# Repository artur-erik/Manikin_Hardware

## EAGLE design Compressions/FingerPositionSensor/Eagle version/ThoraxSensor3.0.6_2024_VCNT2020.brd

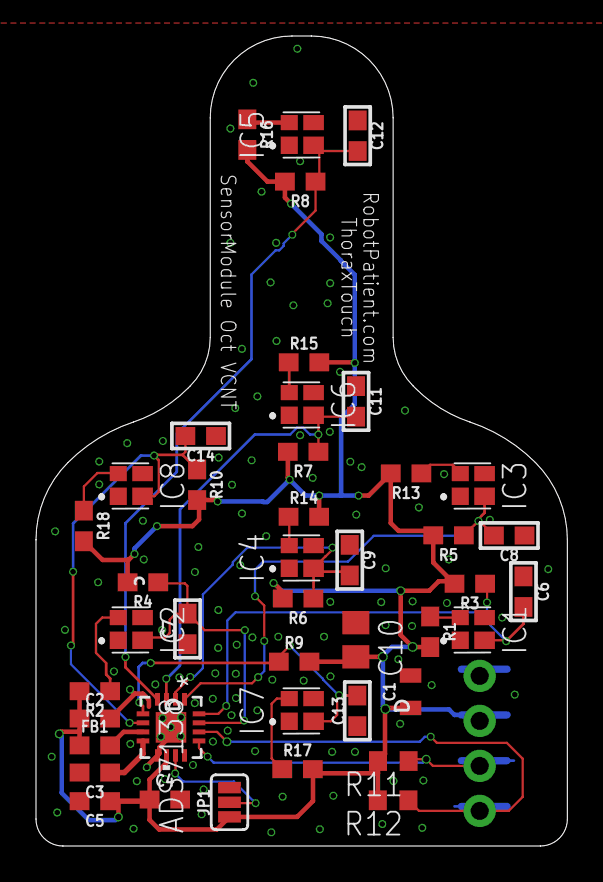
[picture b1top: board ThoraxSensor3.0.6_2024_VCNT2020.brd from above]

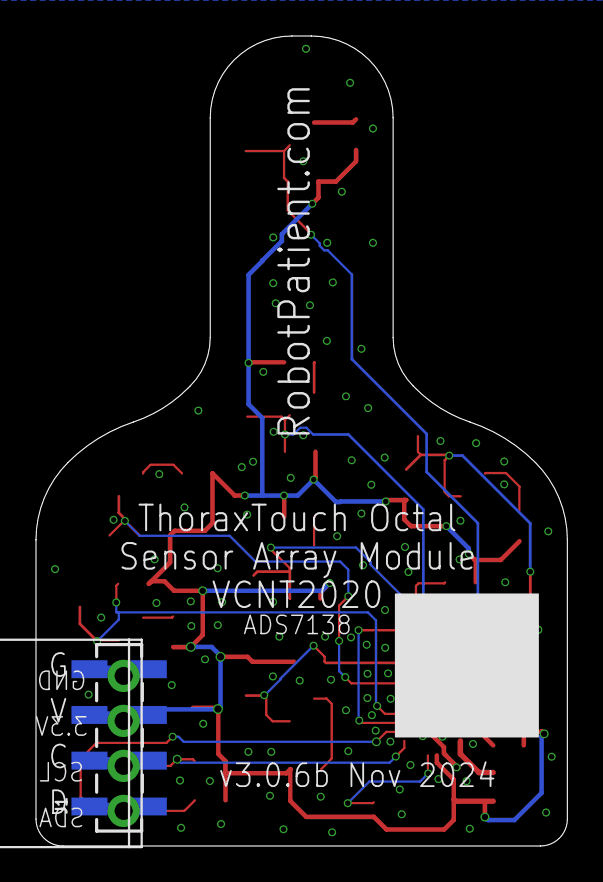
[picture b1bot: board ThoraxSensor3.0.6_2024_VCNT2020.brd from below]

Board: 2 copper layers, 29.5 x 45.0 mm, 45 parts (2 on the bottom side), 23 nets.

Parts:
C1: 10uF; 0805
C2, C3, C4: 1.0uF; 0603
C5: 100pF; 0603
C6, C7, C8, C9, C11, C12, C13, C14: 0.1uF; 0603
C10: 10µF; C0805
FB1: 30Ω; 0603
IC1, IC2, IC3, IC4, IC5, IC6, IC7, IC8: VCNT2020
J1: 1X04_SMD_STRAIGHT_COMBO; 1X04_SMD_VERTICAL_COMBO
JP1: JUMPER-SMT_3_1-NC_PASTE_SILK; SMT-JUMPER_3_1-NC_PASTE_SILK
R1, R2, R13, R14, R15, R16, R17, R18: 180; 0603
R3, R4, R5, R6, R7, R8, R9, R10: 10k; 0603
R11, R12: 4k7; R0603
U$9: ADS7138; QFN_8IRTER_TEX
U$13: PHOENIX_PTSM_M4_TH_ANGLEMIRRORED_SILK_I2C; PTSM_M4_TH_ANGLE_NEUTRAL_MIRRORED

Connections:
3.3V: C1.1, C2.1, C4.1, C5.1, C10.2, FB1.1, J1.3, JP1.1, R1.2, R2.2, R3.2, R4.2, R5.2, R6.2, R7.2, R8.2, R9.2, R10.2, R11.2, R12.2, R13.2, R14.2, R15.2, R16.2, R17.2, R18.2, U$9.10, U$13.P2
ADDR: JP1.2, U$9.11
DECAP: C3.1, U$9.8
GND: C1.2, C2.2, C3.2, C4.2, C5.2, C6.1, C7.1, C8.1, C9.1, C10.1, C11.1, C12.1, C13.1, C14.1, IC1.1, IC1.4, IC2.1, IC2.4, IC3.1, IC3.4, IC4.1, IC4.4, IC5.1, IC5.4, IC6.1, IC6.4, IC7.1, IC7.4, IC8.1, IC8.4, J1.4, JP1.3, U$9.9, U$9.17, U$13.P1
unnamed: IC1.3, R1.1
unnamed: IC2.3, R2.1
unnamed: IC3.3, R13.1
unnamed: IC4.3, R14.1
unnamed: IC6.3, R15.1
unnamed: IC5.3, R16.1
unnamed: IC7.3, R17.1
unnamed: IC8.3, R18.1
unnamed: FB1.2, U$9.7
S1: C6.2, IC1.2, R3.1, U$9.16
S2: C7.2, IC2.2, R4.1, U$9.15
S3: C8.2, IC3.2, R5.1, U$9.1
S4: C9.2, IC4.2, R6.1, U$9.2
S5: C11.2, IC6.2, R7.1, U$9.3
S6: C12.2, IC5.2, R8.1, U$9.4
S7: C13.2, IC7.2, R9.1, U$9.5
S8: C14.2, IC8.2, R10.1, U$9.6
SCL: J1.2, R11.1, U$9.13, U$13.P3
SDA: J1.1, R12.1, U$9.14, U$13.P4

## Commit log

2026-03-20 Initial update
2026-03-20 Initial update 2
2026-03-20 Voltage regulation
2026-03-30 1st version SensorHub
2026-04-03 MYRGM080200C41RA
2026-04-04 ASCODV-24.000MHZ-LR-T3
2026-04-05 New connector BM46B-12DP-0.35V(53)
2026-04-06 New testPoints and Res filter
2026-04-06 Mirrored connector
2026-04-06 Audio jumper
2026-04-09 New hierarchy
2026-04-09 TCAN334
2026-04-12 32k oscillator
2026-04-12 FTSH
2026-04-15 New_USB_2.0
2026-04-15 PCB 1st upd
2026-04-16 PCB upd 2
2026-04-16 PCB_1.0
2026-04-17 Fix 17.04
2026-04-17 Fix2 17.04
2026-04-17 JLCPCB limits
2026-04-27 PCB fix
2026-04-27 Text fix
2026-04-27 Diff_Pressure_Sensor
2026-04-29 Vesrion 2
2026-04-30 MPN + CC fix
2026-04-30 MPN + CC fix2
2026-05-10 DP/DM
2026-05-17 v 2.3
2026-05-17 lib fix
2026-05-17 Compression 1
2026-05-17 Sensors

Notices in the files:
parts and their libraries:
SparkFun-Resistors: Licensing: CC v3.0 Share-Alike You are welcome to use this library for commercial purposes.
SparkFun-Connectors: Licensing: Creative Commons ShareAlike 4.0 International - https://creativecommons.org/licenses/by-sa/4.0
